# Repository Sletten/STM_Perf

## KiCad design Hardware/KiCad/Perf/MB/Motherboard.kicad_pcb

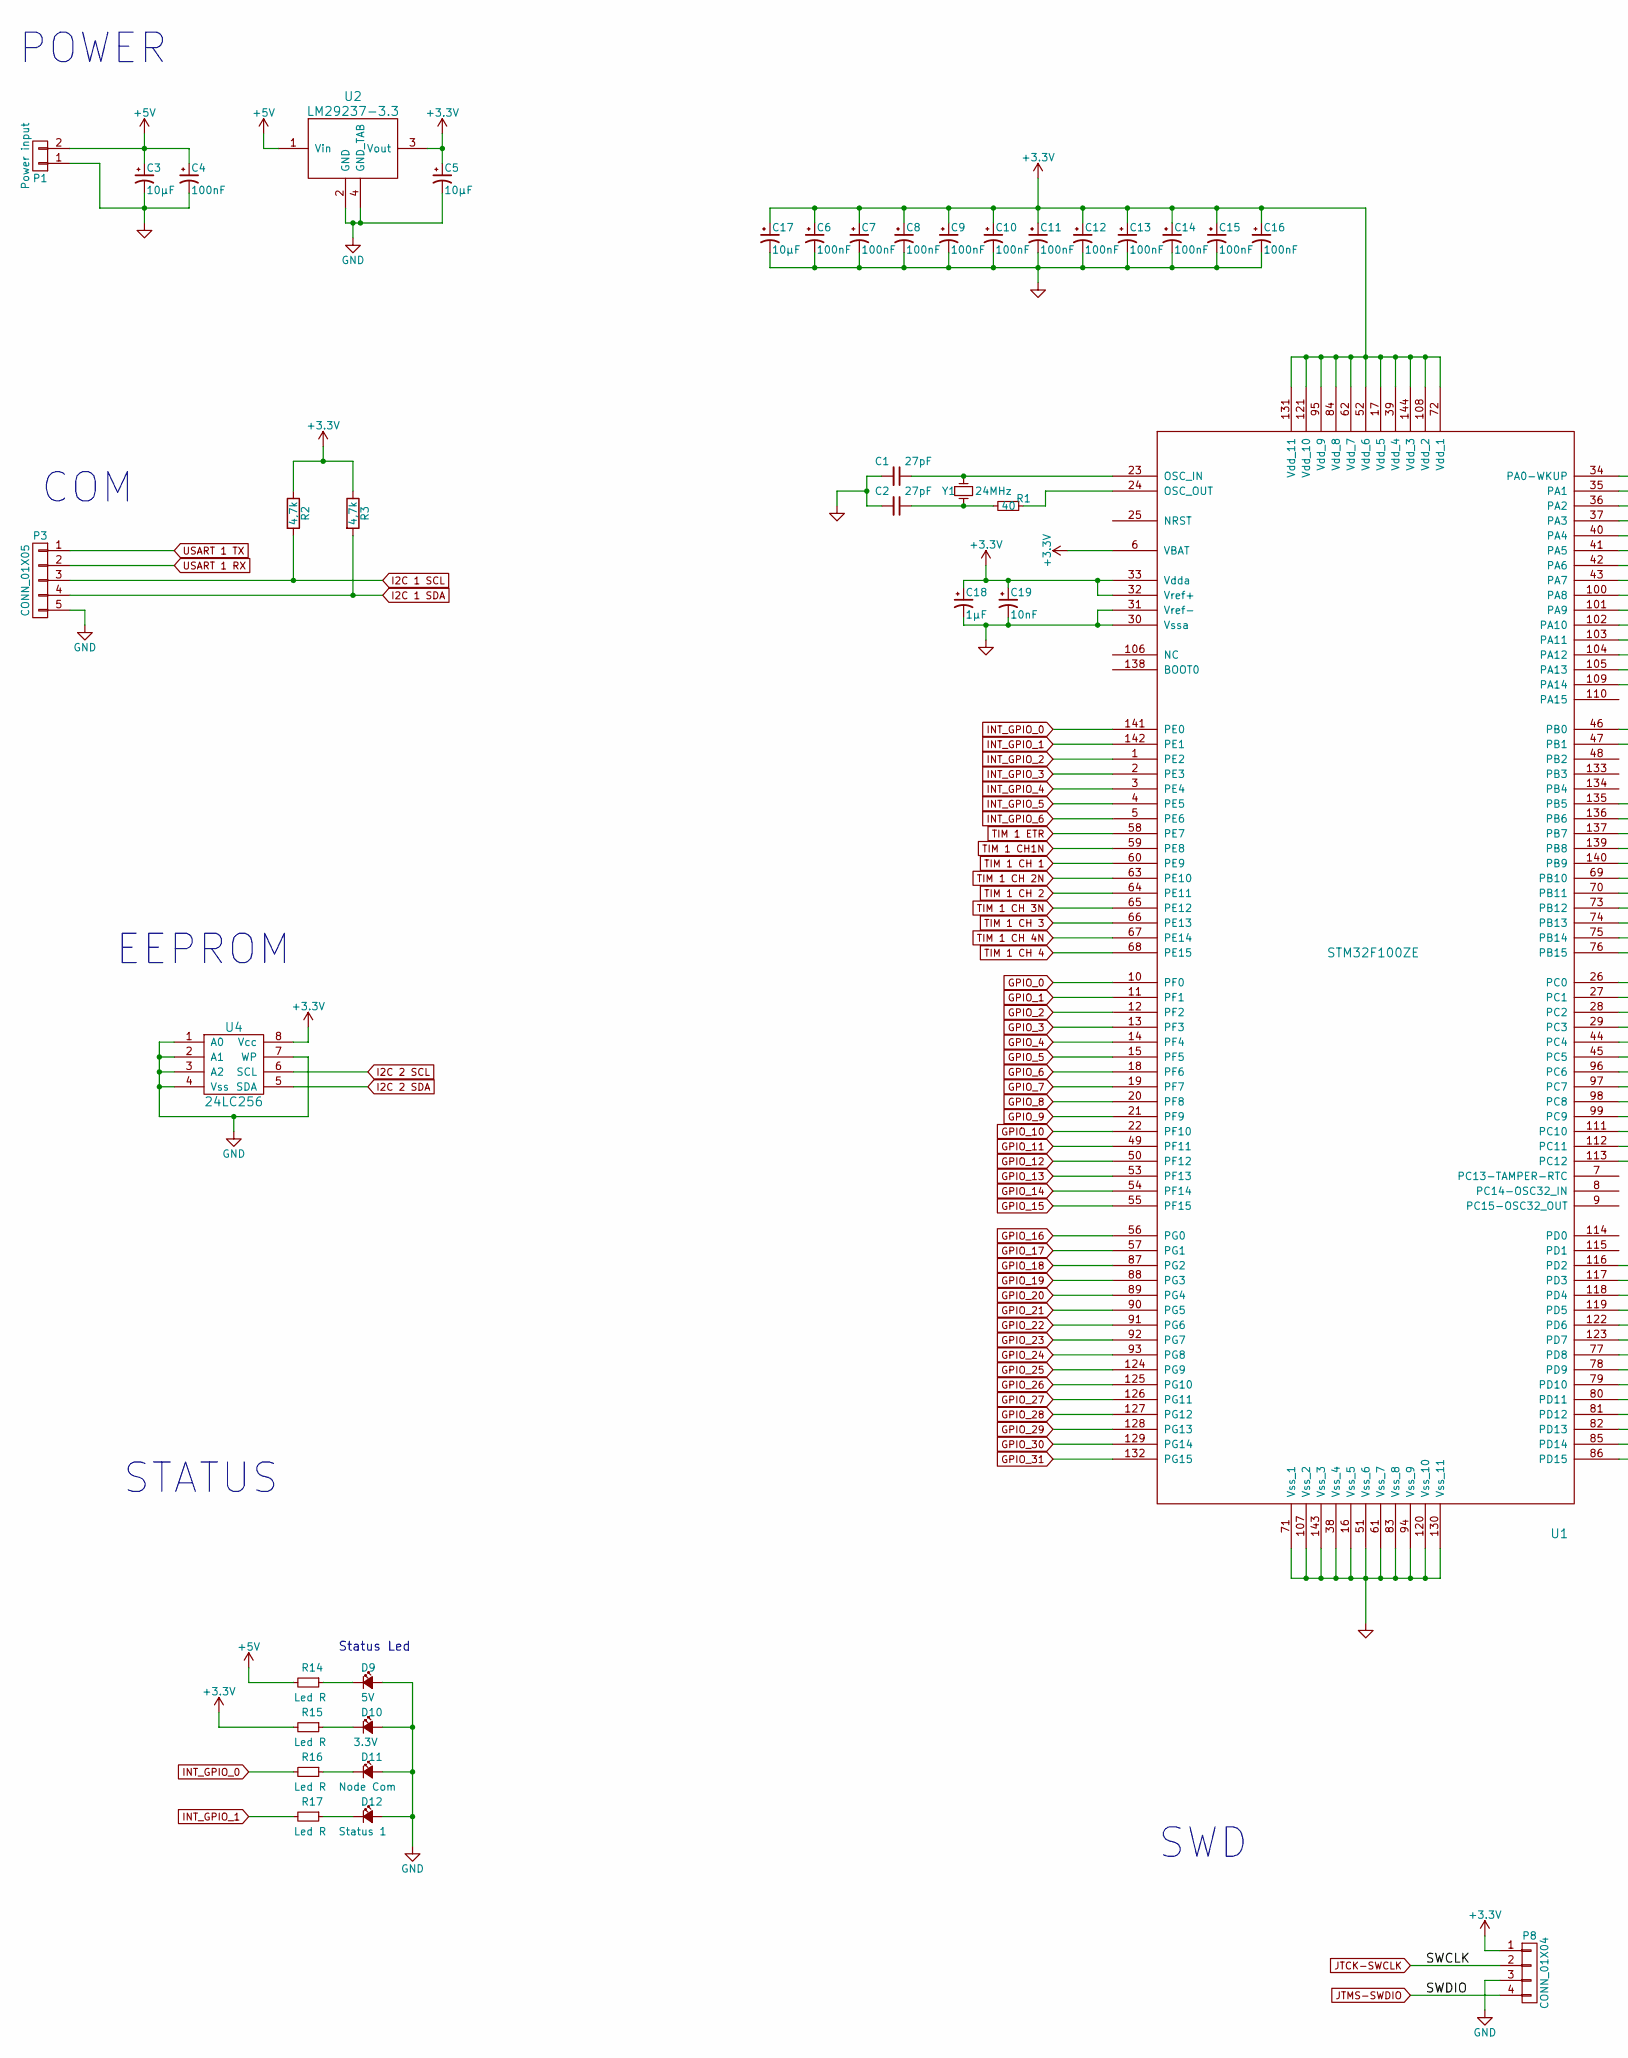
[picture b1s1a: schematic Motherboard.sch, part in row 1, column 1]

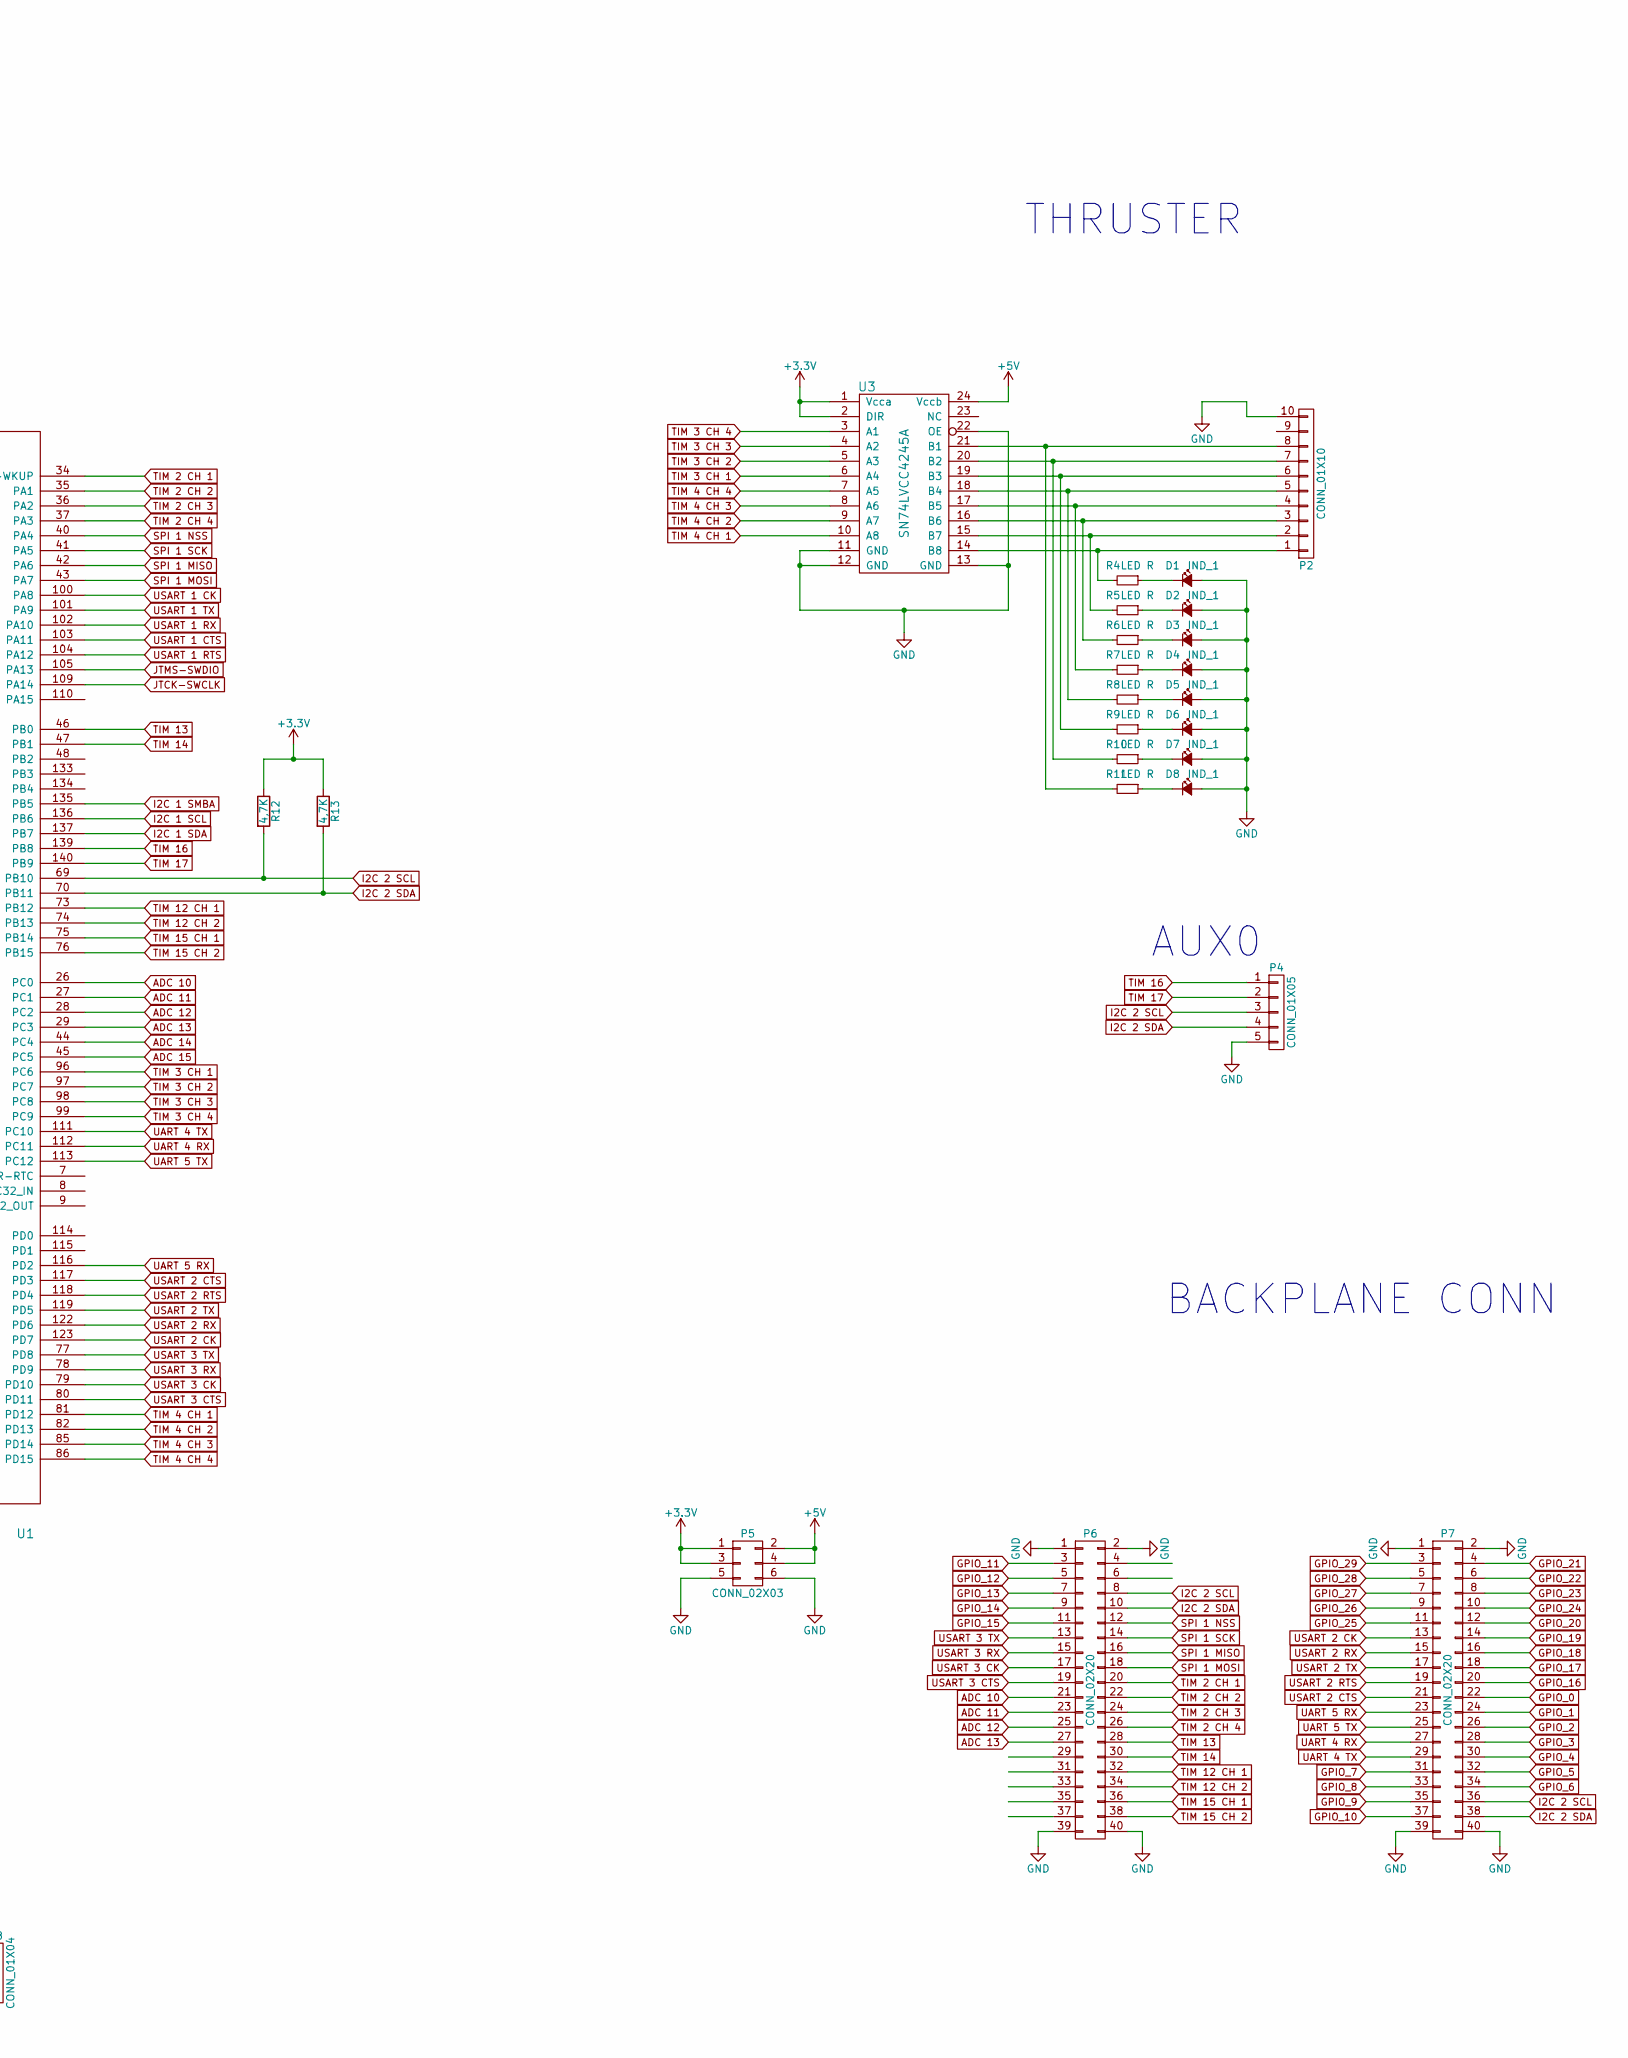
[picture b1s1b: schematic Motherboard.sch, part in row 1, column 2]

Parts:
C1, C2: 27pF
C3, C5, C17: 10µF
C4, C6, C7, C8, C9, C10, C11, C12, C13, C14, C15, C16: 100nF
C18: 1µF
C19: 10nF
D1, D2, D3, D4, D5, D6, D7, D8: IND_1
D9: 5V
D10: 3.3V
D11: Node Com
D12: Status 1
P1: Power input
P2: CONN_01X10
P3, P4: CONN_01X05
P5: CONN_02X03
P6, P7: CONN_02X20
P8: CONN_01X04
R1: 40
R2, R3: 4,7k
R4, R5, R6, R7, R8, R9, R10, R11: LED R
R12, R13: 4,7K
R14, R15, R16, R17: Led R
U1: STM32F100ZE
U2: LM29237-3.3
U3: SN74LVCC4245A
U4: 24LC256
Y1: 24MHz

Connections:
+3V3: C5.1, C6.1, C7.1, C8.1, C9.1, C10.1, C11.1, C12.1, C13.1, C14.1, C15.1, C16.1, C17.1, C18.1, C19.1, P5.1, P5.3, P8.1, R2.1, R3.1, R12.1, R13.1, R15.2, U1.6 (VBAT), U1.17 (Vdd_5), U1.32 (Vref+), U1.33 (Vdda), U1.39 (Vdd_4), U1.52 (Vdd_6), U1.62 (Vdd_7), U1.72 (Vdd_1), U1.84 (Vdd_8), U1.95 (Vdd_9), U1.108 (Vdd_2), U1.121 (Vdd_10), U1.131 (Vdd_11), U1.144 (Vdd_3), U2.3 (Vout), U3.1 (Vcca), U3.2 (DIR), U4.8 (Vcc)
+5V: C3.1, C4.1, P1.2, P5.2, P5.4, R14.2, U2.1 (Vin), U3.24 (Vccb)
ADC 10: P6.21, U1.26 (PC0)
ADC 11: P6.23, U1.27 (PC1)
ADC 12: P6.25, U1.28 (PC2)
ADC 13: P6.27, U1.29 (PC3)
ADC 14: U1.44 (PC4)
ADC 15: U1.45 (PC5)
GND: C1.2, C2.2, C3.2, C4.2, C5.2, C6.2, C7.2, C8.2, C9.2, C10.2, C11.2, C12.2, C13.2, C14.2, C15.2, C16.2, C17.2, C18.2, C19.2, D1.2 (A), D2.2 (A), D3.2 (A), D4.2 (A), D5.2 (A), D6.2 (A), D7.2 (A), D8.2 (A), D9.2 (A), D10.2 (A), D11.2 (A), D12.2 (A), P1.1, P2.10, P3.5, P4.5, P5.5, P5.6, P6.1, P6.2, P6.39, P6.40, P7.1, P7.2, P7.39, P7.40, P8.3, U1.16 (Vss_5), U1.30 (Vssa), U1.31 (Vref-), U1.38 (Vss_4), U1.51 (Vss_6), U1.61 (Vss_7), U1.71 (Vss_1), U1.83 (Vss_8), U1.94 (Vss_9), U1.107 (Vss_2), U1.120 (Vss_10), U1.130 (Vss_11), U1.143 (Vss_3), U2.2 (GND), U2.4 (GND_TAB), U3.11 (GND), U3.12 (GND), U3.13 (GND), U3.22 (OE), U4.1 (A0), U4.2 (A1), U4.3 (A2), U4.4 (Vss), U4.7 (WP)
GPIO_0: P7.22, U1.10 (PF0)
GPIO_1: P7.24, U1.11 (PF1)
GPIO_2: P7.26, U1.12 (PF2)
GPIO_3: P7.28, U1.13 (PF3)
GPIO_4: P7.30, U1.14 (PF4)
GPIO_5: P7.32, U1.15 (PF5)
GPIO_6: P7.34, U1.18 (PF6)
GPIO_7: P7.31, U1.19 (PF7)
GPIO_8: P7.33, U1.20 (PF8)
GPIO_9: P7.35, U1.21 (PF9)
GPIO_10: P7.37, U1.22 (PF10)
GPIO_11: P6.3, U1.49 (PF11)
GPIO_12: P6.5, U1.50 (PF12)
GPIO_13: P6.7, U1.53 (PF13)
GPIO_14: P6.9, U1.54 (PF14)
GPIO_15: P6.11, U1.55 (PF15)
GPIO_16: P7.20, U1.56 (PG0)
GPIO_17: P7.18, U1.57 (PG1)
GPIO_18: P7.16, U1.87 (PG2)
GPIO_19: P7.14, U1.88 (PG3)
GPIO_20: P7.12, U1.89 (PG4)
GPIO_21: P7.4, U1.90 (PG5)
GPIO_22: P7.6, U1.91 (PG6)
GPIO_23: P7.8, U1.92 (PG7)
GPIO_24: P7.10, U1.93 (PG8)
GPIO_25: P7.11, U1.124 (PG9)
GPIO_26: P7.9, U1.125 (PG10)
GPIO_27: P7.7, U1.126 (PG11)
GPIO_28: P7.5, U1.127 (PG12)
GPIO_29: P7.3, U1.128 (PG13)
GPIO_30: U1.129 (PG14)
GPIO_31: U1.132 (PG15)
I2C 1 SCL: P3.3, R2.2, U1.136 (PB6)
I2C 1 SDA: P3.4, R3.2, U1.137 (PB7)
I2C 1 SMBA: U1.135 (PB5)
I2C 2 SCL: P4.3, P6.8, P7.36, R12.2, U1.69 (PB10), U4.6 (SCL)
I2C 2 SDA: P4.4, P6.10, P7.38, R13.2, U1.70 (PB11), U4.5 (SDA)
INT_GPIO_0: R16.2, U1.141 (PE0)
INT_GPIO_1: R17.2, U1.142 (PE1)
INT_GPIO_2: U1.1 (PE2)
INT_GPIO_3: U1.2 (PE3)
INT_GPIO_4: U1.3 (PE4)
INT_GPIO_5: U1.4 (PE5)
INT_GPIO_6: U1.5 (PE6)
JTCK-SWCLK: P8.2, U1.109 (PA14)
JTMS-SWDIO: P8.4, U1.105 (PA13)
unnamed: C1.1, U1.23 (OSC_IN), Y1.1
unnamed: C2.1, R1.2, Y1.2
unnamed: D1.1 (K), R4.1
unnamed: D2.1 (K), R5.1
unnamed: D3.1 (K), R6.1
unnamed: D4.1 (K), R7.1
unnamed: D5.1 (K), R8.1
unnamed: D6.1 (K), R9.1
unnamed: D7.1 (K), R10.1
unnamed: D8.1 (K), R11.1
unnamed: D9.1 (K), R14.1
unnamed: D10.1 (K), R15.1
unnamed: D11.1 (K), R16.1
unnamed: D12.1 (K), R17.1
unnamed: P2.1, R4.2, U3.14 (B8)
unnamed: P2.2, R5.2, U3.15 (B7)
unnamed: P2.3, R6.2, U3.16 (B6)
unnamed: P2.4, R7.2, U3.17 (B5)
unnamed: P2.5, R8.2, U3.18 (B4)
unnamed: P2.6, R9.2, U3.19 (B3)
unnamed: P2.7, R10.2, U3.20 (B2)
unnamed: P2.8, R11.2, U3.21 (B1)
unnamed: R1.1, U1.24 (OSC_OUT)
SPI 1 MISO: P6.16, U1.42 (PA6)
SPI 1 MOSI: P6.18, U1.43 (PA7)
SPI 1 NSS: P6.12, U1.40 (PA4)
SPI 1 SCK: P6.14, U1.41 (PA5)
TIM 1 CH1N: U1.59 (PE8)
TIM 1 CH 1: U1.60 (PE9)
TIM 1 CH 2: U1.64 (PE11)
TIM 1 CH 2N: U1.63 (PE10)
TIM 1 CH 3: U1.66 (PE13)
TIM 1 CH 3N: U1.65 (PE12)
TIM 1 CH 4: U1.68 (PE15)
TIM 1 CH 4N: U1.67 (PE14)
TIM 1 ETR: U1.58 (PE7)
TIM 2 CH 1: P6.20, U1.34 (PA0-WKUP)
TIM 2 CH 2: P6.22, U1.35 (PA1)
TIM 2 CH 3: P6.24, U1.36 (PA2)
TIM 2 CH 4: P6.26, U1.37 (PA3)
TIM 3 CH 1: U1.96 (PC6), U3.6 (A4)
TIM 3 CH 2: U1.97 (PC7), U3.5 (A3)
TIM 3 CH 3: U1.98 (PC8), U3.4 (A2)
TIM 3 CH 4: U1.99 (PC9), U3.3 (A1)
TIM 4 CH 1: U1.81 (PD12), U3.10 (A8)
TIM 4 CH 2: U1.82 (PD13), U3.9 (A7)
TIM 4 CH 3: U1.85 (PD14), U3.8 (A6)
TIM 4 CH 4: U1.86 (PD15), U3.7 (A5)
TIM 12 CH 1: P6.32, U1.73 (PB12)
TIM 12 CH 2: P6.34, U1.74 (PB13)
TIM 13: P6.28, U1.46 (PB0)
TIM 14: P6.30, U1.47 (PB1)
TIM 15 CH 1: P6.36, U1.75 (PB14)
TIM 15 CH 2: P6.38, U1.76 (PB15)
TIM 16: P4.1, U1.139 (PB8)
TIM 17: P4.2, U1.140 (PB9)
UART 4 RX: P7.27, U1.112 (PC11)
UART 4 TX: P7.29, U1.111 (PC10)
UART 5 RX: P7.23, U1.116 (PD2)
UART 5 TX: P7.25, U1.113 (PC12)
USART 1 CK: U1.100 (PA8)
USART 1 CTS: U1.103 (PA11)
USART 1 RTS: U1.104 (PA12)
USART 1 RX: P3.2, U1.102 (PA10)
USART 1 TX: P3.1, U1.101 (PA9)
USART 2 CK: P7.13, U1.123 (PD7)
USART 2 CTS: P7.21, U1.117 (PD3)
USART 2 RTS: P7.19, U1.118 (PD4)
USART 2 RX: P7.15, U1.122 (PD6)
USART 2 TX: P7.17, U1.119 (PD5)
USART 3 CK: P6.17, U1.79 (PD10)
USART 3 CTS: P6.19, U1.80 (PD11)
USART 3 RX: P6.15, U1.78 (PD9)
USART 3 TX: P6.13, U1.77 (PD8)

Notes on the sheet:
POWER
COM
THRUSTER
AUX0
BACKPLANE CONN
EEPROM
STATUS
Status Led
SWD

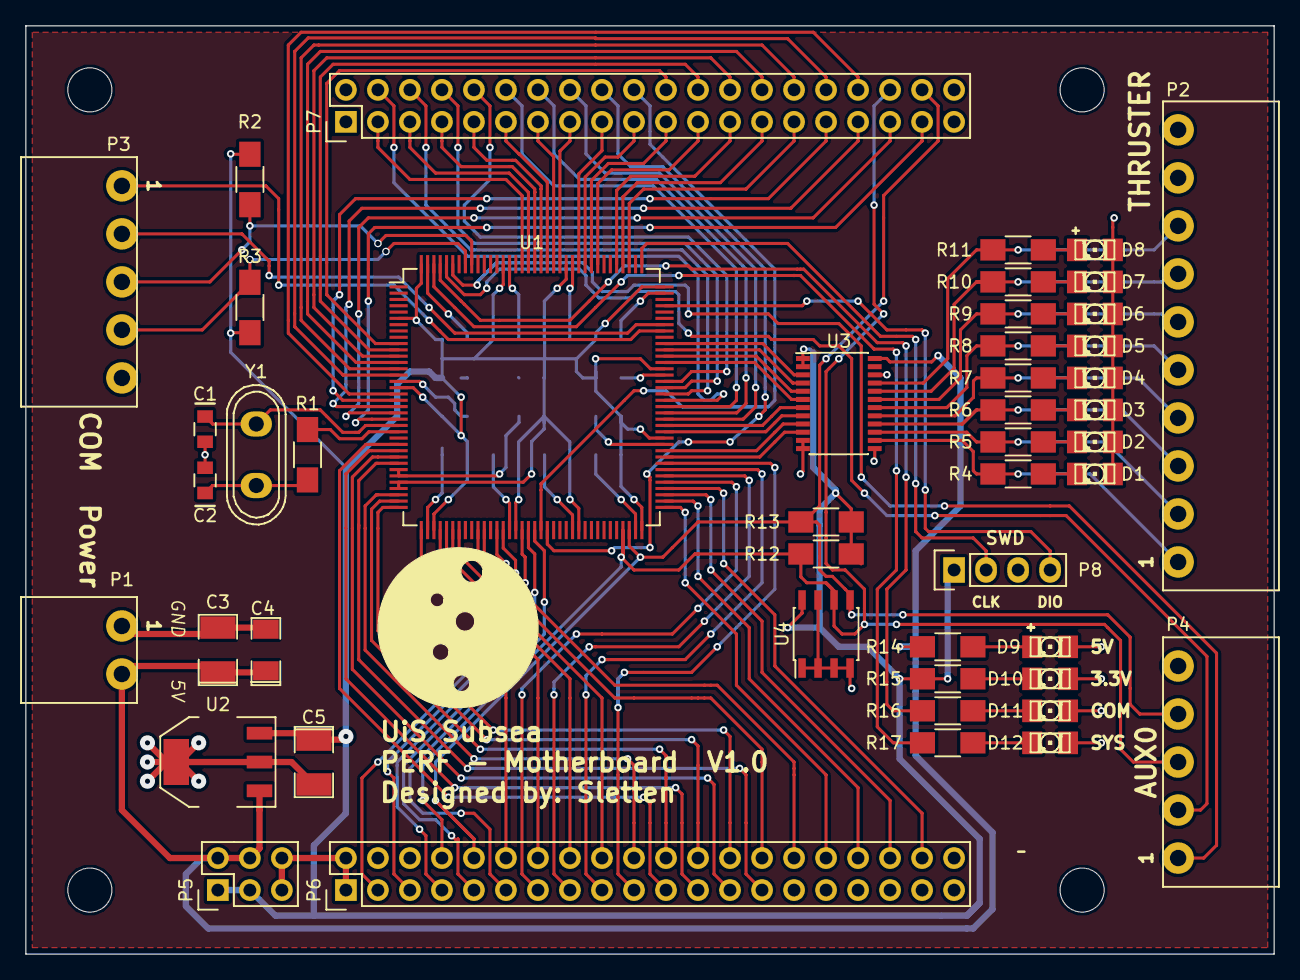
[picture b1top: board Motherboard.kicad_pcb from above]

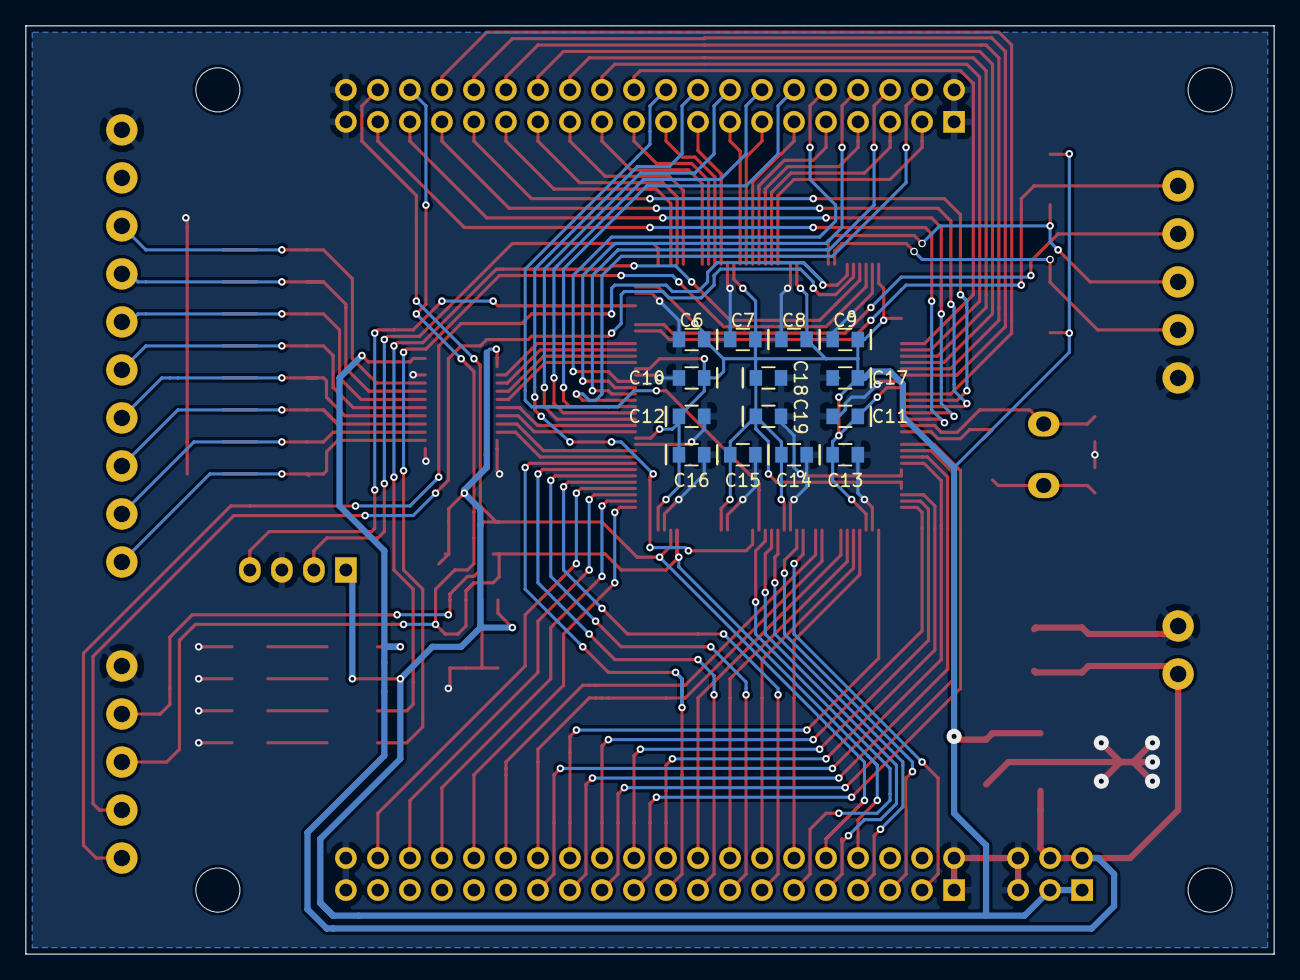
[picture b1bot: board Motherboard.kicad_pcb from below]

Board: 2 copper layers, 99.1 x 73.7 mm, 61 parts (14 on the bottom side), 107 nets.

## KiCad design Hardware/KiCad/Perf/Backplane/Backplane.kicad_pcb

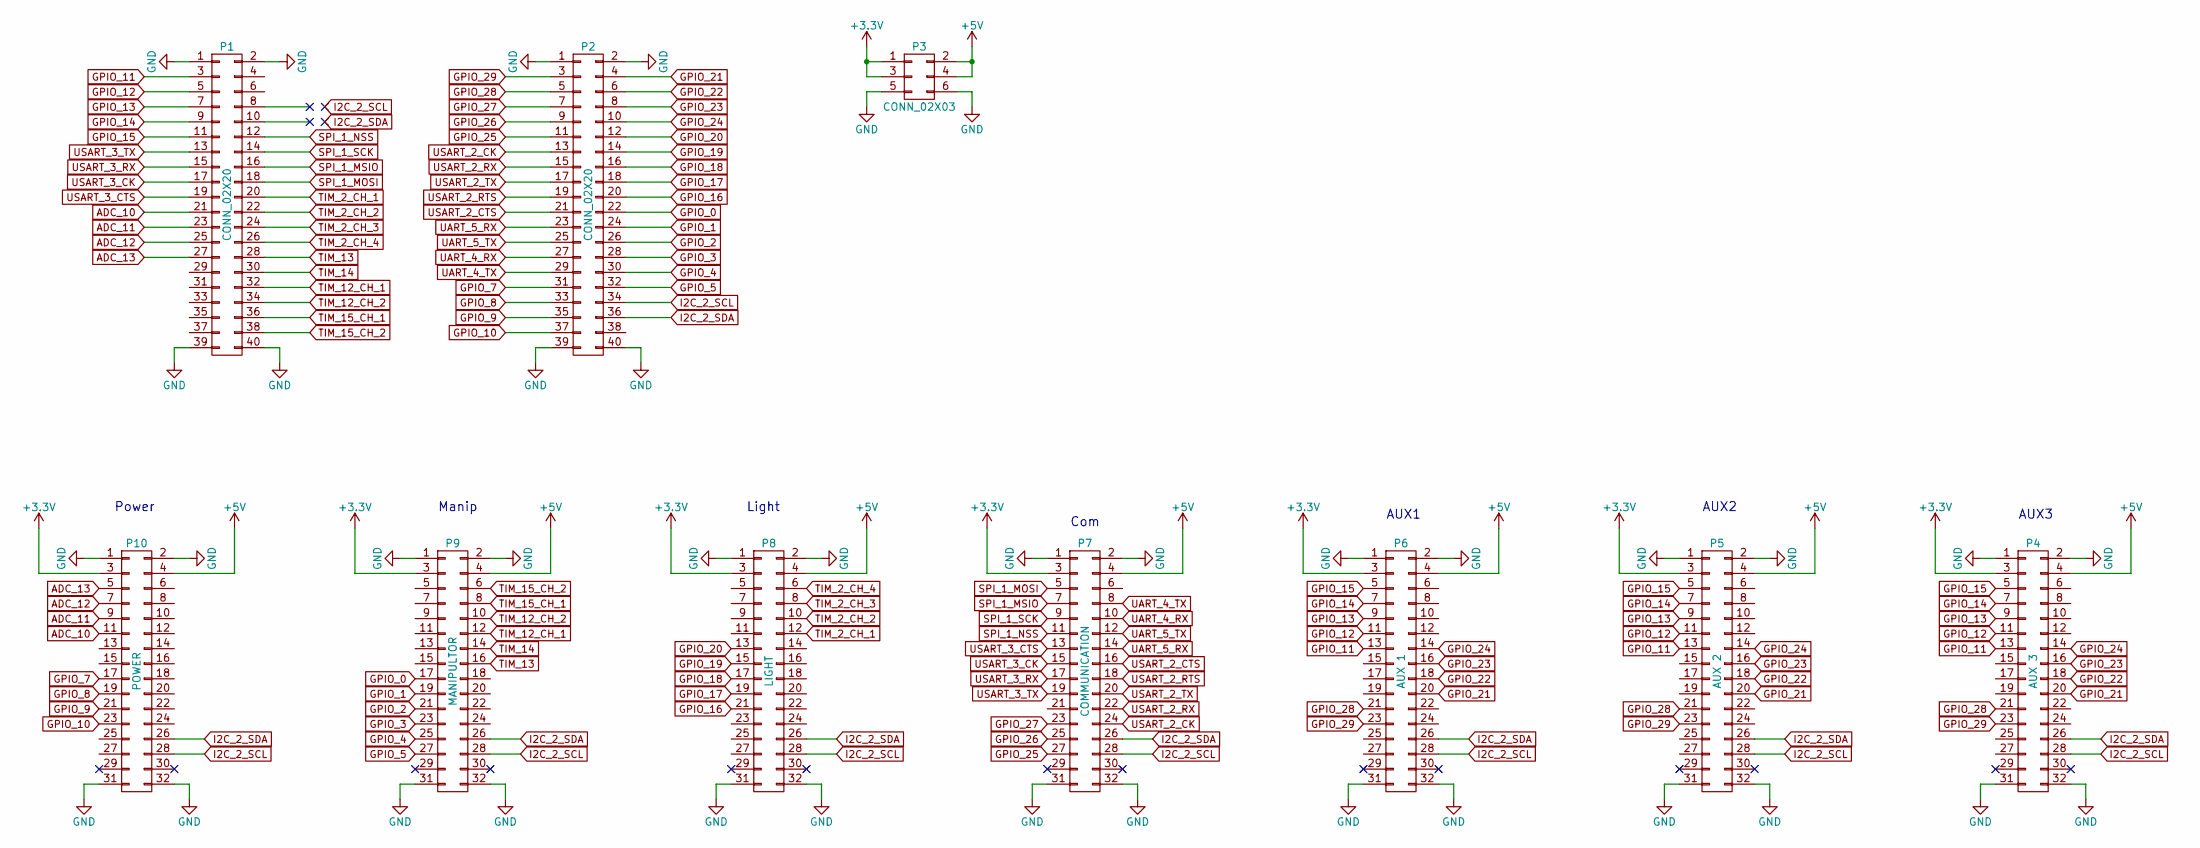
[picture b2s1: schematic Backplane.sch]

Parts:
P1, P2: CONN_02X20
P3: CONN_02X03
P4: AUX 3
P5: AUX 2
P6: AUX 1
P7: COMMUNICATION
P8: LIGHT
P9: MANIPULTOR
P10: POWER

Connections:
+3V3: P3.1, P3.3, P4.3, P5.3, P6.3, P7.3, P8.3, P9.3, P10.3
+5V: P3.2, P3.4, P4.4, P5.4, P6.4, P7.4, P8.4, P9.4, P10.4
ADC_10: P1.21, P10.11
ADC_11: P1.23, P10.9
ADC_12: P1.25, P10.7
ADC_13: P1.27, P10.5
GND: P1.1, P1.2, P1.39, P1.40, P2.1, P2.2, P2.39, P2.40, P3.5, P3.6, P4.1, P4.2, P4.31, P4.32, P5.1, P5.2, P5.31, P5.32, P6.1, P6.2, P6.31, P6.32, P7.1, P7.2, P7.31, P7.32, P8.1, P8.2, P8.31, P8.32, P9.1, P9.2, P9.31, P9.32, P10.1, P10.2, P10.31, P10.32
GPIO_0: P2.22, P9.17
GPIO_1: P2.24, P9.19
GPIO_2: P2.26, P9.21
GPIO_3: P2.28, P9.23
GPIO_4: P2.30, P9.25
GPIO_5: P2.32, P9.27
GPIO_7: P2.31, P10.17
GPIO_8: P2.33, P10.19
GPIO_9: P2.35, P10.21
GPIO_10: P2.37, P10.23
GPIO_11: P1.3, P4.13, P5.13, P6.13
GPIO_12: P1.5, P4.11, P5.11, P6.11
GPIO_13: P1.7, P4.9, P5.9, P6.9
GPIO_14: P1.9, P4.7, P5.7, P6.7
GPIO_15: P1.11, P4.5, P5.5, P6.5
GPIO_16: P2.20, P8.21
GPIO_17: P2.18, P8.19
GPIO_18: P2.16, P8.17
GPIO_19: P2.14, P8.15
GPIO_20: P2.12, P8.13
GPIO_21: P2.4, P4.20, P5.20, P6.20
GPIO_22: P2.6, P4.18, P5.18, P6.18
GPIO_23: P2.8, P4.16, P5.16, P6.16
GPIO_24: P2.10, P4.14, P5.14, P6.14
GPIO_25: P2.11, P7.27
GPIO_26: P2.9, P7.25
GPIO_27: P2.7, P7.23
GPIO_28: P2.5, P4.21, P5.21, P6.21
GPIO_29: P2.3, P4.23, P5.23, P6.23
I2C_2_SCL: P2.34, P4.28, P5.28, P6.28, P7.28, P8.28, P9.28, P10.28
I2C_2_SDA: P2.36, P4.26, P5.26, P6.26, P7.26, P8.26, P9.26, P10.26
SPI_1_MOSI: P1.18, P7.5
SPI_1_MSIO: P1.16, P7.7
SPI_1_NSS: P1.12, P7.11
SPI_1_SCK: P1.14, P7.9
TIM_2_CH_1: P1.20, P8.12
TIM_2_CH_2: P1.22, P8.10
TIM_2_CH_3: P1.24, P8.8
TIM_2_CH_4: P1.26, P8.6
TIM_12_CH_1: P1.32, P9.12
TIM_12_CH_2: P1.34, P9.10
TIM_13: P1.28, P9.16
TIM_14: P1.30, P9.14
TIM_15_CH_1: P1.36, P9.8
TIM_15_CH_2: P1.38, P9.6
UART_4_RX: P2.27, P7.10
UART_4_TX: P2.29, P7.8
UART_5_RX: P2.23, P7.14
UART_5_TX: P2.25, P7.12
USART_2_CK: P2.13, P7.24
USART_2_CTS: P2.21, P7.16
USART_2_RTS: P2.19, P7.18
USART_2_RX: P2.15, P7.22
USART_2_TX: P2.17, P7.20
USART_3_CK: P1.17, P7.15
USART_3_CTS: P1.19, P7.13
USART_3_RX: P1.15, P7.17
USART_3_TX: P1.13, P7.19

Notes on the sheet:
Power
Manip
Light
Com
AUX1
AUX2
AUX3

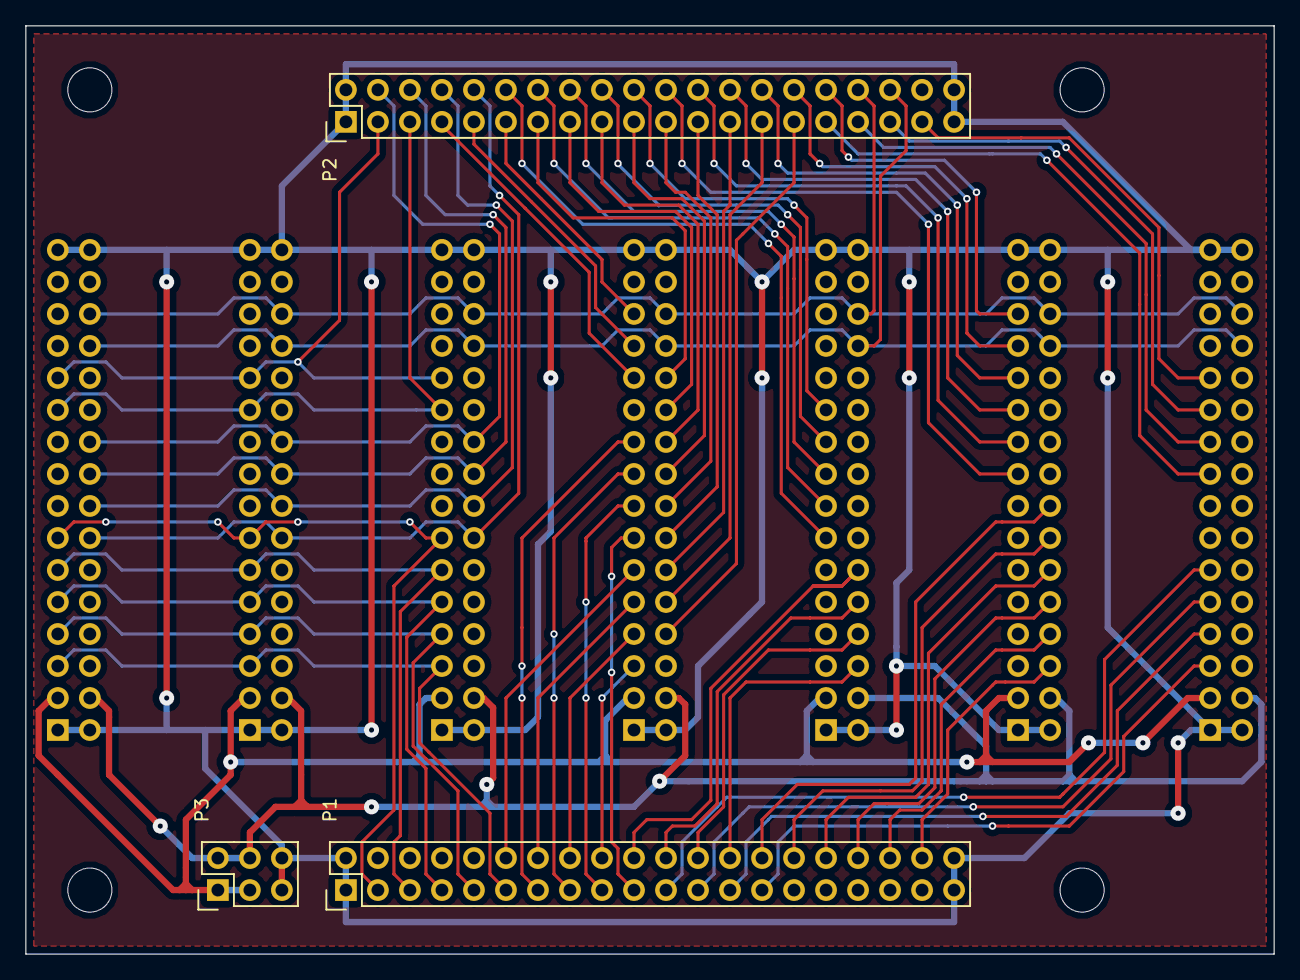
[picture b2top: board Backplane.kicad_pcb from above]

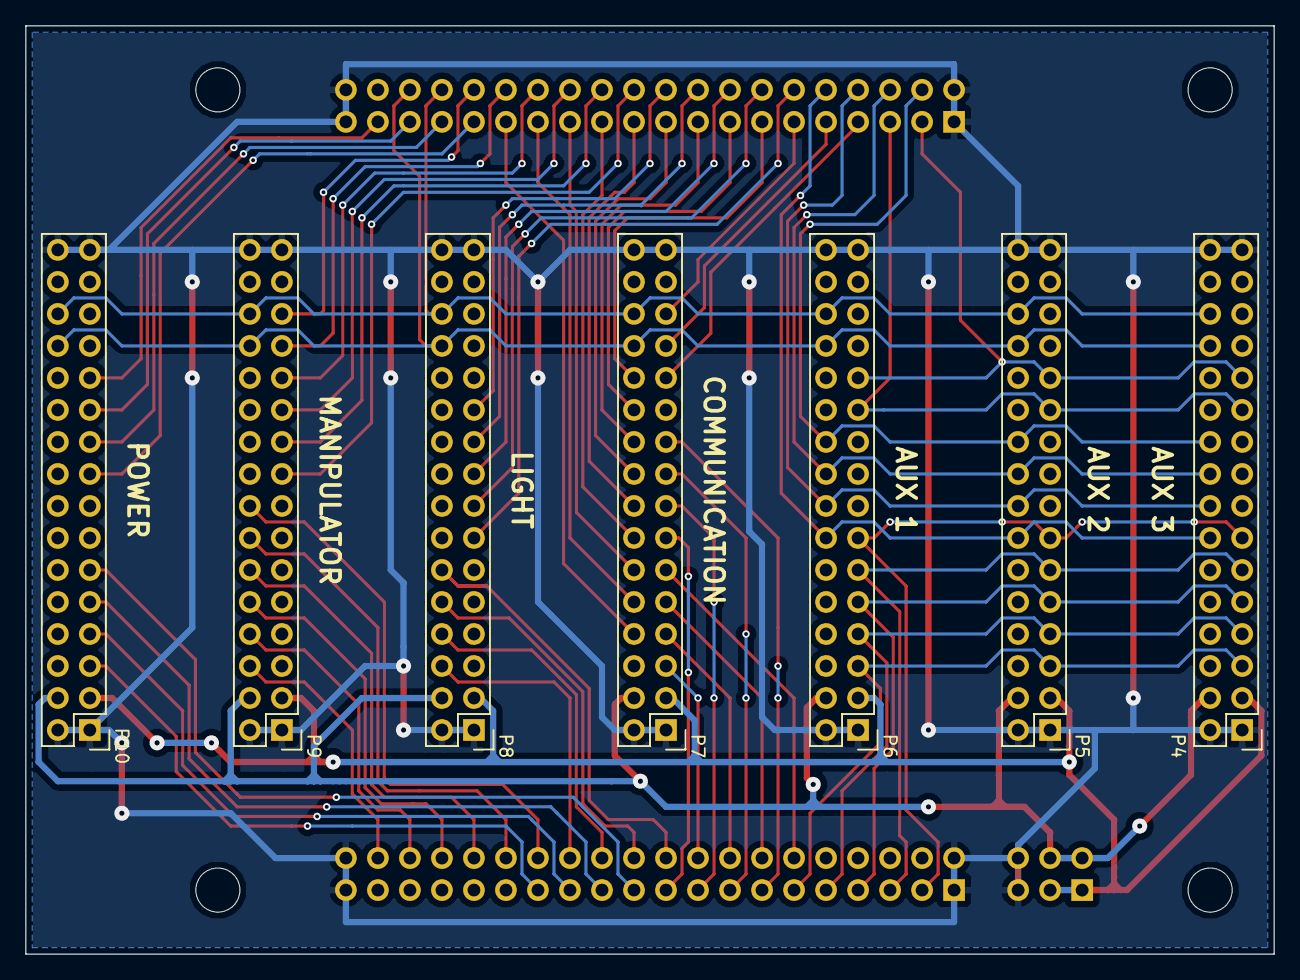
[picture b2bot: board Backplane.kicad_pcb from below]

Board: 2 copper layers, 99.1 x 73.7 mm, 10 parts (7 on the bottom side), 65 nets.

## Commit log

2015-05-01 Initial commit from existing work
2015-05-01 sorted into hardware and software
2015-05-01 testing
2015-05-20 Started electronics layout, planing of PERF modules
2015-05-23 sdfghjkl
    sdfghjklø
2015-05-25 laying out motherboard and backplane
2015-05-27 updated footprints and some layout
2015-05-28 updated BOM
2015-05-31 Sterted on software
2015-05-31 Small change to USART 2 pin layout from MB to Backplane
2015-05-31 gpio configuration done
2015-05-31 working in com setup
2015-05-31 Fungerende kode, setter servo via uart
2015-06-02 completed backplane pcb
2015-06-03 Created gerber files for ordering
2015-06-13 working on thruster code
2015-06-18 some work on communication protocol
2015-06-18 working on thruster system
    Trying to implement highly modular thruster system, but is facing some
    challenges with thruster scaling when maximum thrust is reached
2015-06-21 continued work on thruster control
2015-06-24 updated error in level shifter footprint
2015-06-28 Fixed missign ground connection to level shifter
2015-06-29 fixed adressing error on PERF eeprom
2015-06-30 work on communication protocoll and eeprom data
2015-07-05 updated gerber files
2015-07-20 working on thruster software
2015-07-23 Updated Gerberfiles for produection
2015-07-26 planing com code
2015-08-01 Working on communication software
2015-08-06 More work on scaling thruster vectoring, might have overcomplicated slightly, considering hardcode in the thruster setup
2015-08-14 Working on simplified thruster control
2015-08-29 Fixed fixed-point error in thruster code, and fixed rounding error
2015-08-30 PERF thruster code, and general setup
    Implemented the thruster code to the PERF system, still need to set up
    the control of the pwm outputs.
    Fixed external crystal frequency, was HSE_Value set to 24Mhz, to get
    uart to work propperly. Probably fixed other potential errors.
2015-08-30 com testing
2015-08-31 Started implementing communication protocol
2015-09-05 Working on communication
    Implementing communication protocol
    setting up timer interrupt to catch error in recieving data when taking
    too long.
2015-09-27 startign on i2c communication
2015-10-10 Stuff is working!
    Fixed thruster scaling where dividing by zero, and rounding messed up
    the calculation.
    PWM scaling to fit servo output fixed and working.
2015-10-11 Added read and write byte to EEPROM
2015-10-14 fix for thruster scaling.
    changed temp scale from 16bit to 32bit
2015-10-15 some updats to the explaination of the communication protocol
2015-10-17 Started schematic of power distribution PERF_module
2015-10-18 some modification to clean up thruster code
2015-10-22 Cleaned up thruster code, and added some explaination
    Cleaned up the code, and made it more independent of the system such as
    setting the registers for the timer outputs.
    Some experimental code needs to be tested.
    Added explaination of the code, so should be easier to understand
2015-10-25 Tesing uis subsea logo on pcb design
2015-10-25 More work on thruster code
    Added prototype og esc configurator, needs to be tested and timed
    correctly
    Some polishing on the new untested stuff
2016-05-06 Fixed i2c 1 layout error
    Fixed wrong pin layout for i2c1
